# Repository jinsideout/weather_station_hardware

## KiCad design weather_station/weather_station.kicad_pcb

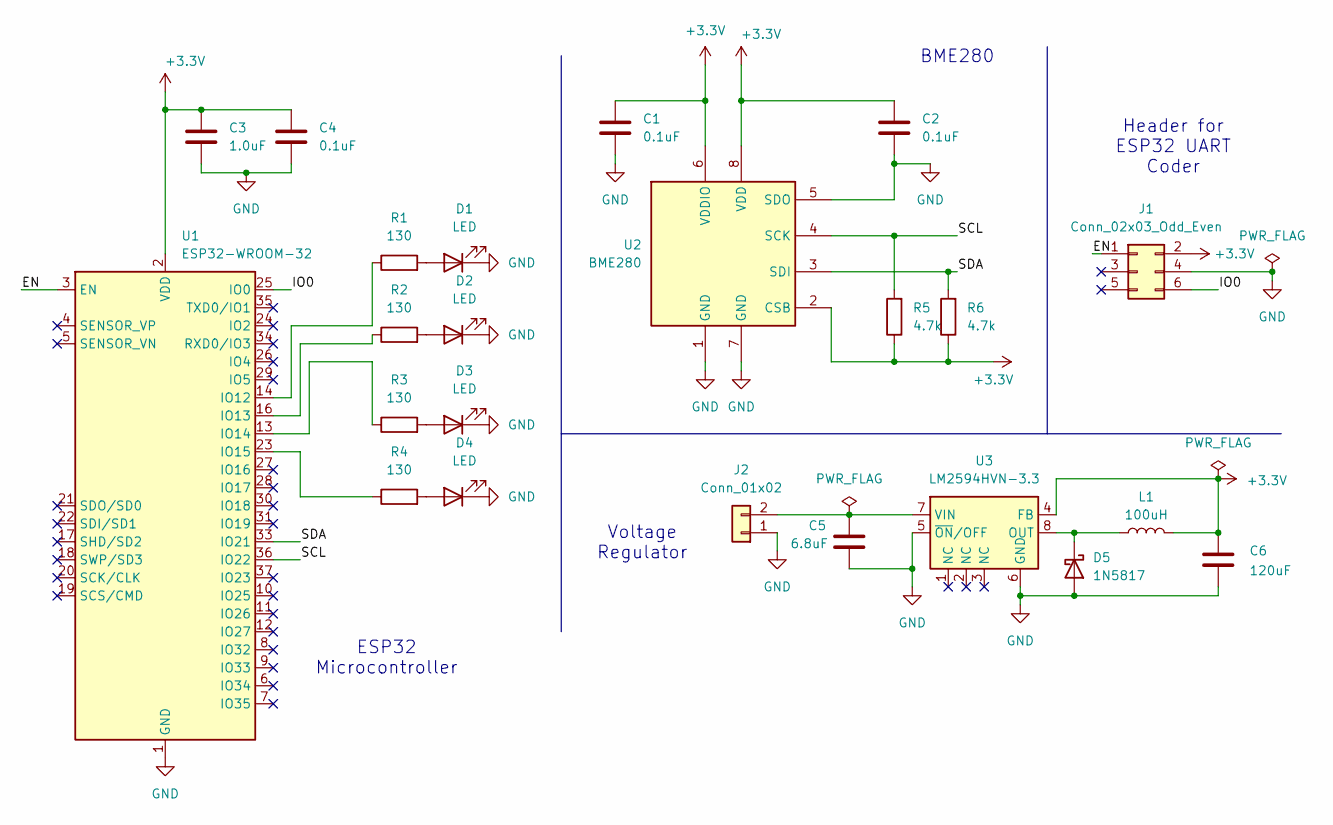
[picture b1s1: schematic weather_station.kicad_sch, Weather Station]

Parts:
C1, C2, C4: 0.1uF; CP_Radial_D10.0mm_P5.00mm
C3: 1.0uF; CP_Radial_D10.0mm_P5.00mm
C5: 6.8uF; CP_Radial_D5.0mm_P2.50mm
C6: 120uF; CP_Radial_D5.0mm_P2.00mm
D1, D2, D3, D4: LED; LED_D3.0mm
D5: 1N5817; D_DO-41_SOD81_P10.16mm_Horizontal
J1: Conn_02x03_Odd_Even; IDC-Header_2x03_P2.54mm_Vertical
J2: Conn_01x02; AMASS_XT60-F_1x02_P7.20mm_Vertical
L1: 100uH; L_Axial_L5.3mm_D2.2mm_P2.54mm_Vertical_Vishay_IM-1
R1, R2, R3, R4: 130; R_Axial_DIN0204_L3.6mm_D1.6mm_P1.90mm_Vertical
R5, R6: 4.7k; R_Axial_DIN0204_L3.6mm_D1.6mm_P1.90mm_Vertical
U1: ESP32-WROOM-32
U2: BME280; Bosch_LGA-8_2.5x2.5mm_P0.65mm_ClockwisePinNumbering
U3: LM2594HVN-3.3; DIP-8_W7.62mm

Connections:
+3.3V: C1.1, C2.1, C3.1, C4.1, C6.1, J1.2, L1.2, R5.1, R6.1, U1.2 (VDD), U2.2 (CSB), U2.6 (VDDIO), U2.8 (VDD), U3.4 (FB)
/EN: J1.1, U1.3 (EN)
/IO0: J1.6, U1.25 (IO0)
/SCL: R5.2, U1.36 (IO22), U2.4 (SCK)
/SDA: R6.2, U1.33 (IO21), U2.3 (SDI)
GND: C1.2, C2.2, C3.2, C4.2, C5.2, C6.2, D1.1 (K), D2.1 (K), D3.1 (K), D4.1 (K), D5.2 (A), J1.4, J2.1, U1.1 (GND), U1.15 (GND), U1.38 (GND), U1.39 (GND), U2.1 (GND), U2.5 (SDO), U2.7 (GND), U3.5 (~ON/OFF), U3.6 (GND)
unnamed: D1.2 (A), R1.2
unnamed: D2.2 (A), R2.2
unnamed: D3.2 (A), R3.2
unnamed: D4.2 (A), R4.2
unnamed: D5.1 (K), L1.1, U3.8 (OUT)
unnamed: C5.1, J2.2, U3.7 (VIN)
unnamed: R1.1, U1.14 (IO12)
unnamed: R2.1, U1.16 (IO13)
unnamed: R3.1, U1.13 (IO14)
unnamed: R4.1, U1.23 (IO15)

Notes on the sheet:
BME280
Voltage Regulator
Header for ESP32 UART Coder
ESP32 Microcontroller

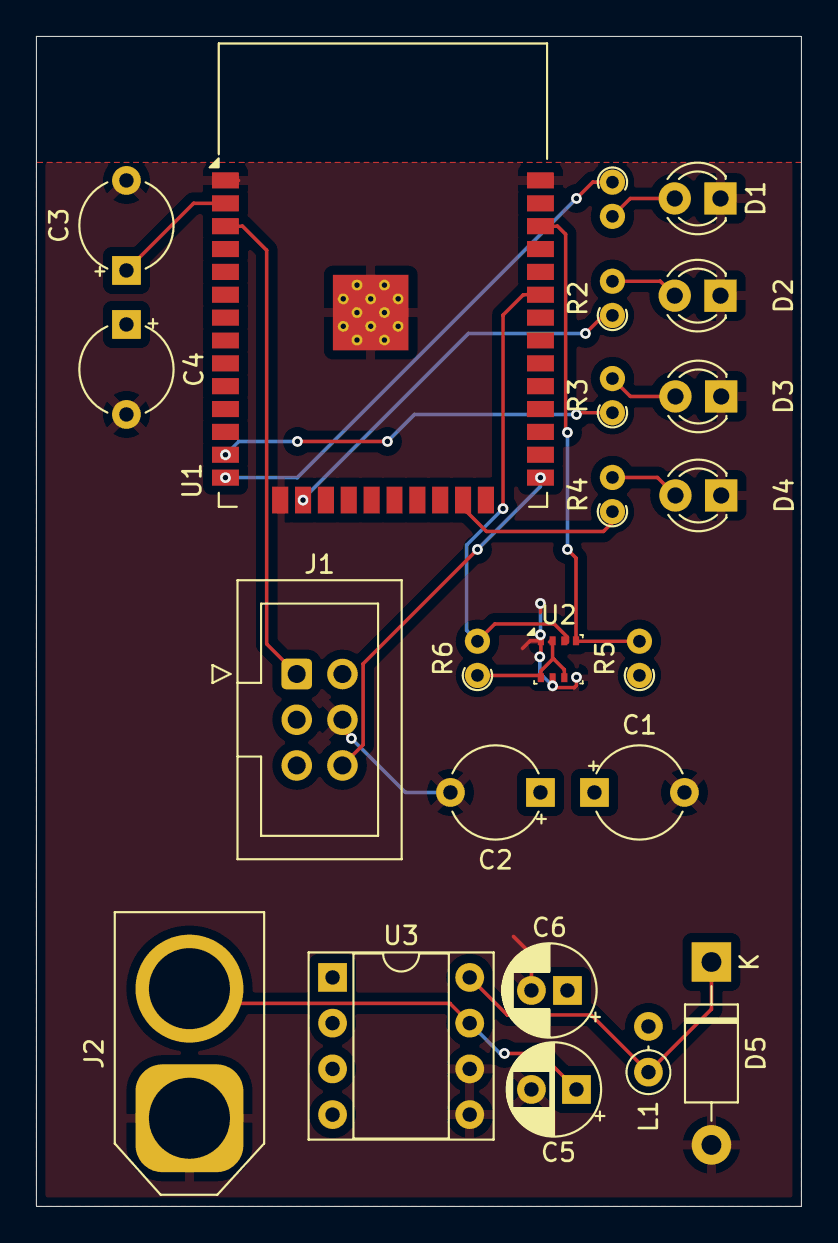
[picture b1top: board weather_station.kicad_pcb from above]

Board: 2 copper layers, 42.5 x 65.0 mm, 23 parts (0 on the bottom side), 16 nets.

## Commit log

2024-07-27 Initial KiCAD schematic
2024-07-27 Added XT60 battery connector
2024-07-28 Assigned footprints
    Assigned footprints to LEDs, resistors, capacitors, and inductor.
2024-07-29 Completed PCB layout
    Note: ESP32 doesn't match footprint warning is due to changing the hole diameter of ground vias.
